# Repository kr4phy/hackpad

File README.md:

# Hackpad by kr4phy
This is my hackpad design.
This pad contains one rotary encoder (including a switch), 8 keys (4*2 matrix), and an OLED screen and uses all GPIO pins.

## Overview
- 8 macro key matrix (4*2)
- Rotary encoder knob with switch
- 0.96" OLED display
- XIAO RP2040 mcu

## Project structure
```
hackpad/
├── LICENSE
├── README.md
│
├── Rotary_Encoder.pretty/            # KiCad encoder footprints
│
├── case/                            # 3d models for case
│   ├── hackpad.f3d                  # Fusion 360 project file
│   ├── hackpad.step                 # STEP model file
│   ├── hackpad_ap242.step            # STEP AP242 file
│   ├── plate-2026-10-29T14_19_29.061Z.dxf
│   └── plate-2026-11-01T02_40_03.895Z.dxf
│
├── kicad_care_package/
│   ├── SK6812MINI-E.kicad_sym
│   ├── XIAO_RP2040.kicad_sym
│   └── footprints.pretty/
│       ├── SK6812MINI-E_fixed.kicad_mod
│       └── XIAO-Generic-Hybrid-14P-2.54-21X17.8MM.kicad_mod
│
└── pcb/                             # Files about PCB design
    ├── DRC.rpt                      # Design Rule Check report
    ├── fp-lib-table
    ├── hackpad.dsn
    ├── hackpad.kicad_pcb
    ├── hackpad.kicad_prl
    ├── hackpad.kicad_pro
    ├── hackpad.kicad_sch
    ├── hackpad.ses
    ├── hackpad_auto_routed.dsn
    ├── sym-lib-table
    ├── sym-lib-table.bak
    └── ~hackpad.kicad_pro.lck
```

## Firmware
Firmware is under development. Not implemented yet, but I planned to make it possible to customize the keymap using only the pad without an external PC. I also planned to create a menu that can be operated with a rotary encoder.

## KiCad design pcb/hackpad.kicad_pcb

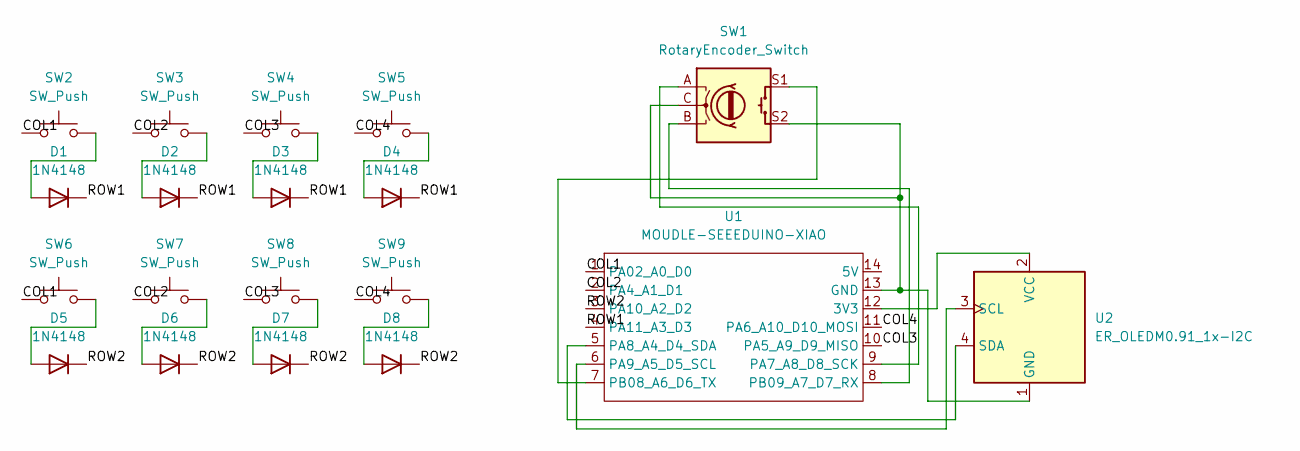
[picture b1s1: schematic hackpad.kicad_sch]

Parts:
D1, D2, D3, D4, D5, D6, D7, D8: 1N4148; D_DO-35_SOD27_P7.62mm_Horizontal
SW1: RotaryEncoder_Switch; RotaryEncoder_Alps_EC11E-Switch_Vertical_H20mm
SW2, SW3, SW4, SW5, SW6, SW7, SW8, SW9: SW_Push; SW_Cherry_MX_1.00u_PCB
U1: MOUDLE-SEEEDUINO-XIAO; XIAO-Generic-Hybrid-14P-2.54-21X17.8MM
U2: ER_OLEDM0.91_1x-I2C

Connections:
/COL1: SW2.1, SW6.1, U1.1 (PA02_A0_D0)
/COL2: SW3.1, SW7.1, U1.2 (PA4_A1_D1)
/COL3: SW4.1, SW8.1, U1.10 (PA5_A9_D9_MISO)
/COL4: SW5.1, SW9.1, U1.11 (PA6_A10_D10_MOSI)
/ROW1: D1.1 (K), D2.1 (K), D3.1 (K), D4.1 (K), U1.4 (PA11_A3_D3)
/ROW2: D5.1 (K), D6.1 (K), D7.1 (K), D8.1 (K), U1.3 (PA10_A2_D2)
unnamed: D1.2 (A), SW2.2
unnamed: D2.2 (A), SW3.2
unnamed: D3.2 (A), SW4.2
unnamed: D4.2 (A), SW5.2
unnamed: D5.2 (A), SW6.2
unnamed: D6.2 (A), SW7.2
unnamed: D7.2 (A), SW8.2
unnamed: D8.2 (A), SW9.2
unnamed: U1.12 (3V3), U2.2 (VCC)
unnamed: SW1.C, SW1.S2, U1.13 (GND), U2.1 (GND)
unnamed: SW1.A, U1.9 (PA7_A8_D8_SCK)
unnamed: U1.5 (PA8_A4_D4_SDA), U2.4 (SDA)
unnamed: U1.6 (PA9_A5_D5_SCL), U2.3 (SCL)
unnamed: SW1.S1, U1.7 (PB08_A6_D6_TX)
unnamed: SW1.B, U1.8 (PB09_A7_D7_RX)

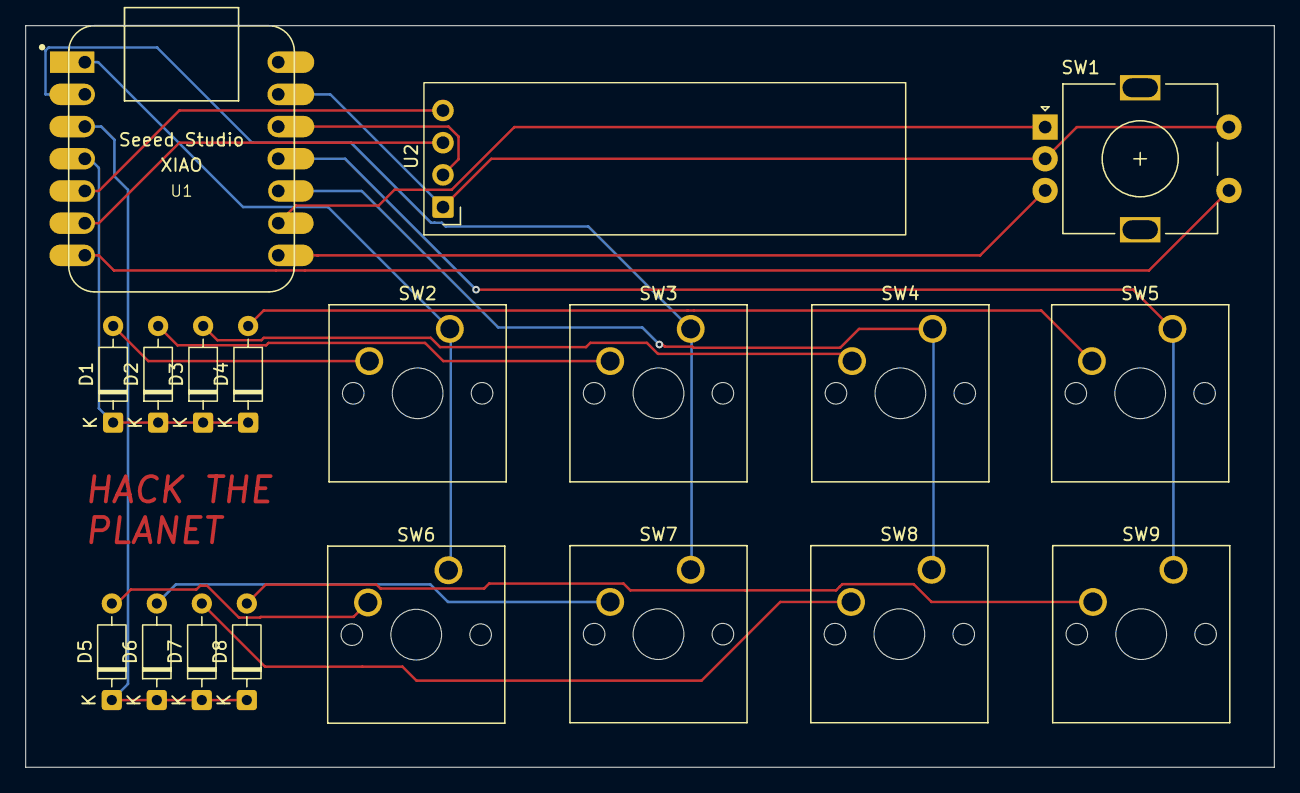
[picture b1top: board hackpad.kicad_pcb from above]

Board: 2 copper layers, 98.5 x 58.5 mm, 19 parts (0 on the bottom side), 21 nets.
